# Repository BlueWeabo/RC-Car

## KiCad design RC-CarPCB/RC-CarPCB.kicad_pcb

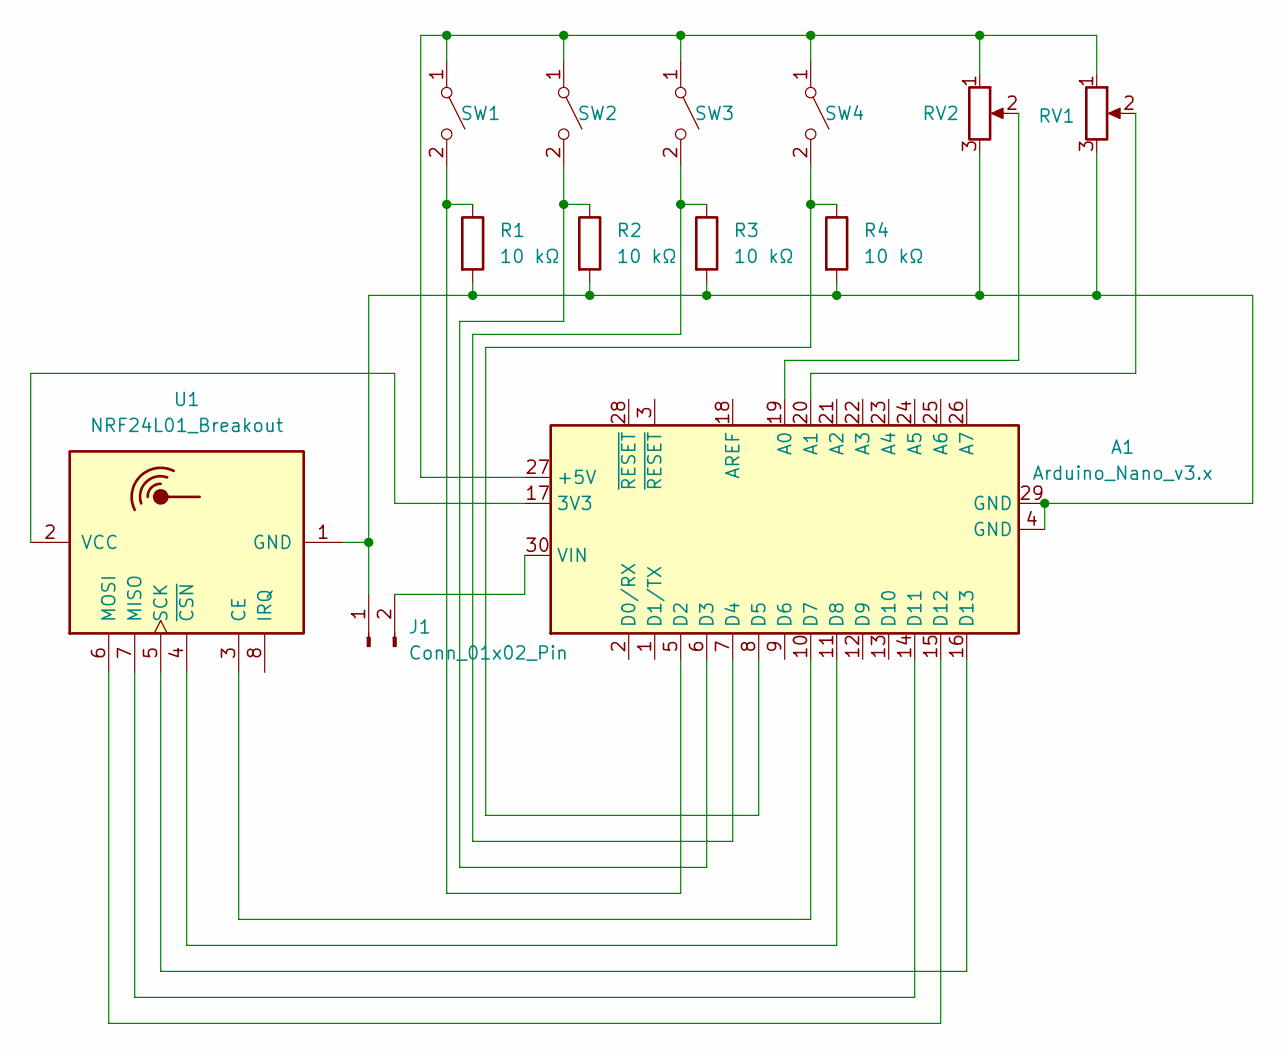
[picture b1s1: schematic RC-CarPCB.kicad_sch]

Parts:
A1: Arduino_Nano_v3.x; Arduino_Nano
J1: Conn_01x02_Pin; JWT_A3963_1x02_P3.96mm_Vertical
R1, R2, R3, R4: 10 kΩ; R_Axial_DIN0204_L3.6mm_D1.6mm_P7.62mm_Horizontal
RV1, RV2: R_Potentiometer; Potentiometer_Bourns_PTA6043_Single_Slide
SW1, SW2, SW3, SW4: SW_SPST; SW_SPST_PTS647_Sx50
U1: NRF24L01_Breakout; nRF24L01_Breakout

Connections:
unnamed: A1.17 (3V3), U1.2 (VCC)
unnamed: A1.27 (+5V), RV1.1, RV2.1, SW1.1 (A), SW2.1 (A), SW3.1 (A), SW4.1 (A)
unnamed: A1.19 (A0), RV2.2
unnamed: A1.20 (A1), RV1.2
unnamed: A1.5 (D2), R1.1, SW1.2 (B)
unnamed: A1.6 (D3), R2.1, SW2.2 (B)
unnamed: A1.7 (D4), R3.1, SW3.2 (B)
unnamed: A1.8 (D5), R4.1, SW4.2 (B)
unnamed: A1.10 (D7), U1.3 (CE)
unnamed: A1.11 (D8), U1.4 (~CSN)
unnamed: A1.14 (D11), U1.7 (MISO)
unnamed: A1.15 (D12), U1.6 (MOSI)
unnamed: A1.16 (D13), U1.5 (SCK)
unnamed: A1.30 (VIN), J1.2
unnamed: A1.4 (GND), A1.29 (GND), J1.1, R1.2, R2.2, R3.2, R4.2, RV1.3, RV2.3, U1.1 (GND)

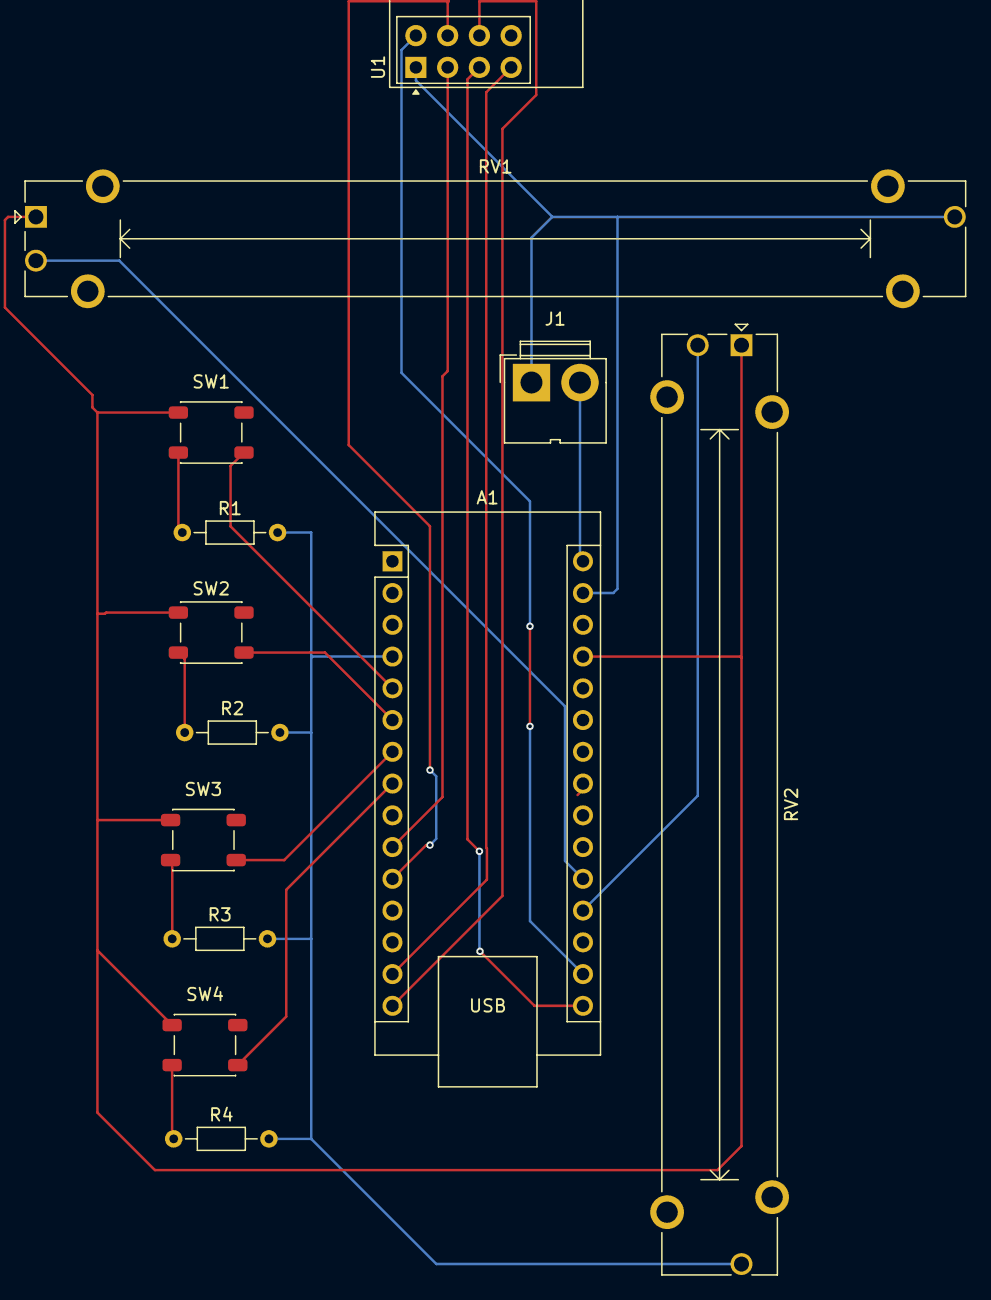
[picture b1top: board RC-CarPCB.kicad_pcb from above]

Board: 2 copper layers, 13 parts (0 on the bottom side), 15 nets.

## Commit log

2025-01-15 initial code
2025-01-16 pcb files
2025-03-15 stuff
2025-03-16 working code
2025-04-22 disable debug
